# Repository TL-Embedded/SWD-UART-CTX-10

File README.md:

# SWD-UART-CTX-10

This is an adaptor for the 10 pin tag-connect cables.

**Output:**
 * TC2050 or EC10 ribbon

**Input:**
 * UART via standard FTDI header
 * SWD via standard 20 pin ARM header
 * Auxilary voltage input

This is compatible with the Tag-Connect `TC2050-ARM2010 ARM 20-pin to TC2050 Adapter` in SWD mode.

# Target pinout

On the target, the TC2050 or EC10 should have the following assignment.

| Pin# | Function   |
| ---- | --------   |
| 1    | VCC_Target |
| 2    | SWDIO      |
| 3    | GND        |
| 4    | SWCLK      |
| 5    | VCC_Aux    |
| 6    | SWO        |
| 7    | TX (to target) |
| 8    | Detect     |
| 9    | RX (from target) |
| 10   | Reset      |

## Detect

This pin is tied to ground on the adaptor - and can be used by the target to sense the presence of the adaptor.

## VCC_Aux

This is tied to the `V+` pin. This is an optional input for providing arbitrary power to the target.

## TX & RX

The Tx and Rx are described with respect to the host, **not the target**.

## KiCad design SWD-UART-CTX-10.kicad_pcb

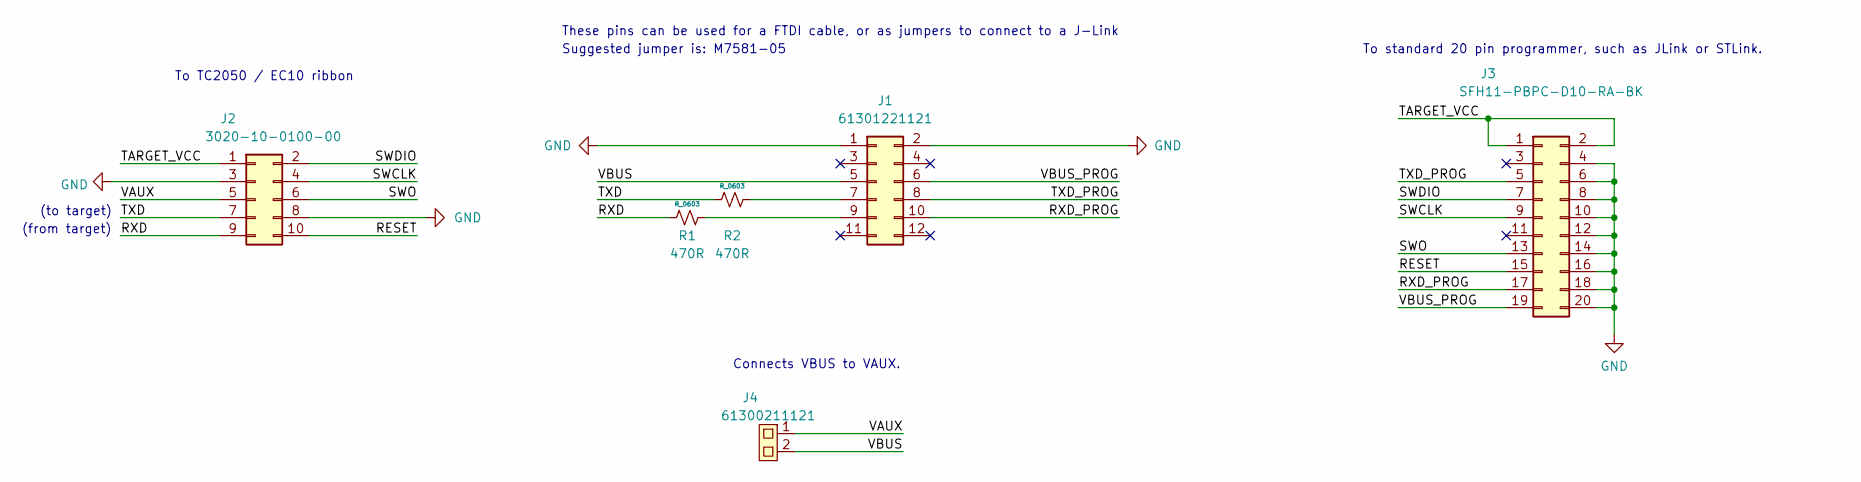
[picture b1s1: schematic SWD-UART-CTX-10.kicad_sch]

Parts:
J1: 61301221121; PinHeader_2x06_P2.54mm_Vertical
J2: 3020-10-0100-00; IDC-Header_2x05_P2.54mm_Vertical
J3: SFH11-PBPC-D10-RA-BK; PinSocket_2x10_P2.54mm_Horizontal
J4: 61300211121; PinHeader_1x02_P2.54mm_Vertical
R1, R2: 470R; R_0603

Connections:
/RESET: J2.10, J3.15
/RXD: J2.9, R1.1
/RXD_PROG: J1.10, J3.17
/SWCLK: J2.4, J3.9
/SWDIO: J2.2, J3.7
/SWO: J2.6, J3.13
/TARGET_VCC: J2.1, J3.1, J3.2
/TXD: J2.7, R2.1
/TXD_PROG: J1.8, J3.5
/VAUX: J2.5, J4.1
/VBUS: J1.5, J4.2
/VBUS_PROG: J1.6, J3.19
GND: J1.1, J1.2, J2.3, J2.8, J3.4, J3.6, J3.8, J3.10, J3.12, J3.14, J3.16, J3.18, J3.20
unnamed: J1.7, R2.2
unnamed: J1.9, R1.2

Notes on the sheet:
Connects VBUS to VAUX.
Suggested jumper is: M7581-05
(to target)
(from target)
To TC2050 / EC10 ribbon
To standard 20 pin programmer, such as JLink or STLink.
These pins can be used for a FTDI cable, or as jumpers to connect to a J-Link

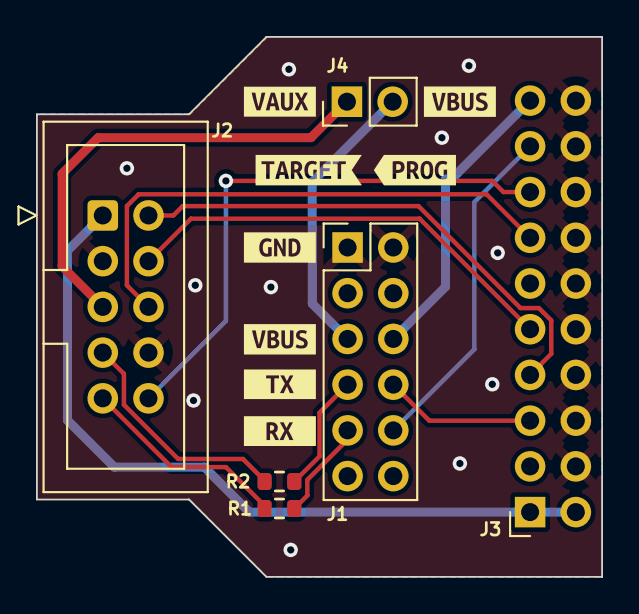
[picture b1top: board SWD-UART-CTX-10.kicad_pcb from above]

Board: 2 copper layers, 31.4 x 30.0 mm, 14 parts (0 on the bottom side), 15 nets.

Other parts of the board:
kibuzzard-653C8A9D: G***; kibuzzard-653C8A9D
kibuzzard-653C8AA8: G***; kibuzzard-653C8AA8
kibuzzard-653C8AB2: G***; kibuzzard-653C8AB2
kibuzzard-653C8ABC: G***; kibuzzard-653C8ABC
kibuzzard-653C8B0E: G***; kibuzzard-653C8B0E
kibuzzard-653C8B17: G***; kibuzzard-653C8B17
kibuzzard-653C8B44: G***; kibuzzard-653C8B44
kibuzzard-653C8BB4: G***; kibuzzard-653C8BB4

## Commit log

2022-11-19 First pass at adaptor
2022-11-19 Just use headers
2022-11-19 Add series R
2022-11-19 Guild the lilly
2022-11-23 Add jumper for vaux to vbus
2022-11-23 Exclude JP1 from BOM
2022-12-22 Removed blatantly false information
2023-10-28 Update for J-Link options
2023-10-28 Commit output scripts
